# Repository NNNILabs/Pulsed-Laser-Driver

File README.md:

# Pulsed Laser Driver

<p align="center">
    <b>Power uncorrupted.</b> -J. Williams
</p>

## Introduction
A good friend of mine was talking about his work at the Solid State Physics lab at TU Berlin. They are currently trying to build upon the work of Japanese researchers regarding UVC lasers. These lasers need short, sharp (that was an English adjective, in EE speak it's "fast rise time") current pulses to be properly evaluated. With The Art of Electronics: The X Chapters by my side, I decided to take this project up, and boy, was it worth it. 
## Project Motivation
Apparently pulsed laser drivers cost upwards of several tens of thousands of Euros, so being able to come up with a a solution (that will probably be orders of magnitude cheaper) would be a much welcome break to the Lab's budget. Since the requirements were not particularly challenging (~250V, 5A, 1us pulses), I decided it would be feasible to try making a pulsed current sink.
## Usage
### Specifications [temp: as promised]:
- 25ns rise/fall times
- 5A peak current
- 250V diode voltage
## List of Files
- Resources: 
  - Infographics
- Hardware: 
  - KiCAD PCB files
- Software:
  - Simulation: LTspice .asc file, libraries
## Application Examples
[under construction]
## Notes
- Laser diodes usually with several volts across them. Since this UVC laser is under on-wafer testing, the methods of supplying power to the die involve high-resistance contacts: needles on pads, hence the need for high voltages.
- The choice of LT1193 was arbitrary - there are op-amps available that are better suited to the task, but I wanted an excuse to use the LT1193 because of its unique inputs which enable it to Kelvin-sense the input signal and feedback from the shunt. 
- Rise time measurements in LTspice of initial simulation using an AO6408 (10nH, 10pF parasitics):

- Rise time measurement with GaN FET (GS66502) (10nH, 10pF parasitics):

- GaN FETs which feature input, output and feedback capacitances that are at least an order of magnitude smaller than their regular silicon counterparts, are ideal for this application. Because of the low input capacitance (and the fact that the input capacitance is bootstrapped by Gm x source shunt resistor), the driving op-amp sees a significantly reduced capacitive load. On resistance and threshold voltage is comparable to a regular small switching MOSFET, but the drain-source breakdown voltage is significantly higher, almost touching 1kV. Of course, regular MOSFETs (or even a cascode to get the best of both worlds - easy drive with lots of transconductance and high-voltage drive capability) can be used with appropriate compensation "for the sake of a challenge", but GaN FETs save a lot of blood, sweat and tears.
- I decided to try using a smaller shunt resistor so the op-amp wouldn't have to swing as much to drive the gate and shunt voltage. This should theoretically increase bandwidth and therefore speed, but it did the opposite. One theory is that the threshold voltage of the MOSFET is much higher than the shunt voltage, so a smaller shunt voltage would mean a larger difference between it and gate threshold, so larger swing to get the same result. But a higher shunt voltage also means higher overall op-amp output, which should have a slowing effect. The answer can be found in AoE X - a higher shunt resistance means a higher bootstrapping voltage across gate-source capacitance through FET transconductance. 

## Links
- https://x.artofelectronics.net/
  - pg. 193 3x.5 "MOSFETs as Linear Transistors"
  - pg. 206 3x.7 "Bandwidth of the Cascode; BJT versus FET"
  - pg. 386 4x.26 "Nodal Loop Analysis: MOSFET Current Source"
- https://www.analog.com/media/en/technical-documentation/data-sheets/1193fb.pdf
- https://www.analog.com/media/en/technical-documentation/application-notes/an133f.pdf
- https://gansystems.com/wp-content/uploads/2022/07/GS-065-008-1-L-DS-Rev-220712.pdf

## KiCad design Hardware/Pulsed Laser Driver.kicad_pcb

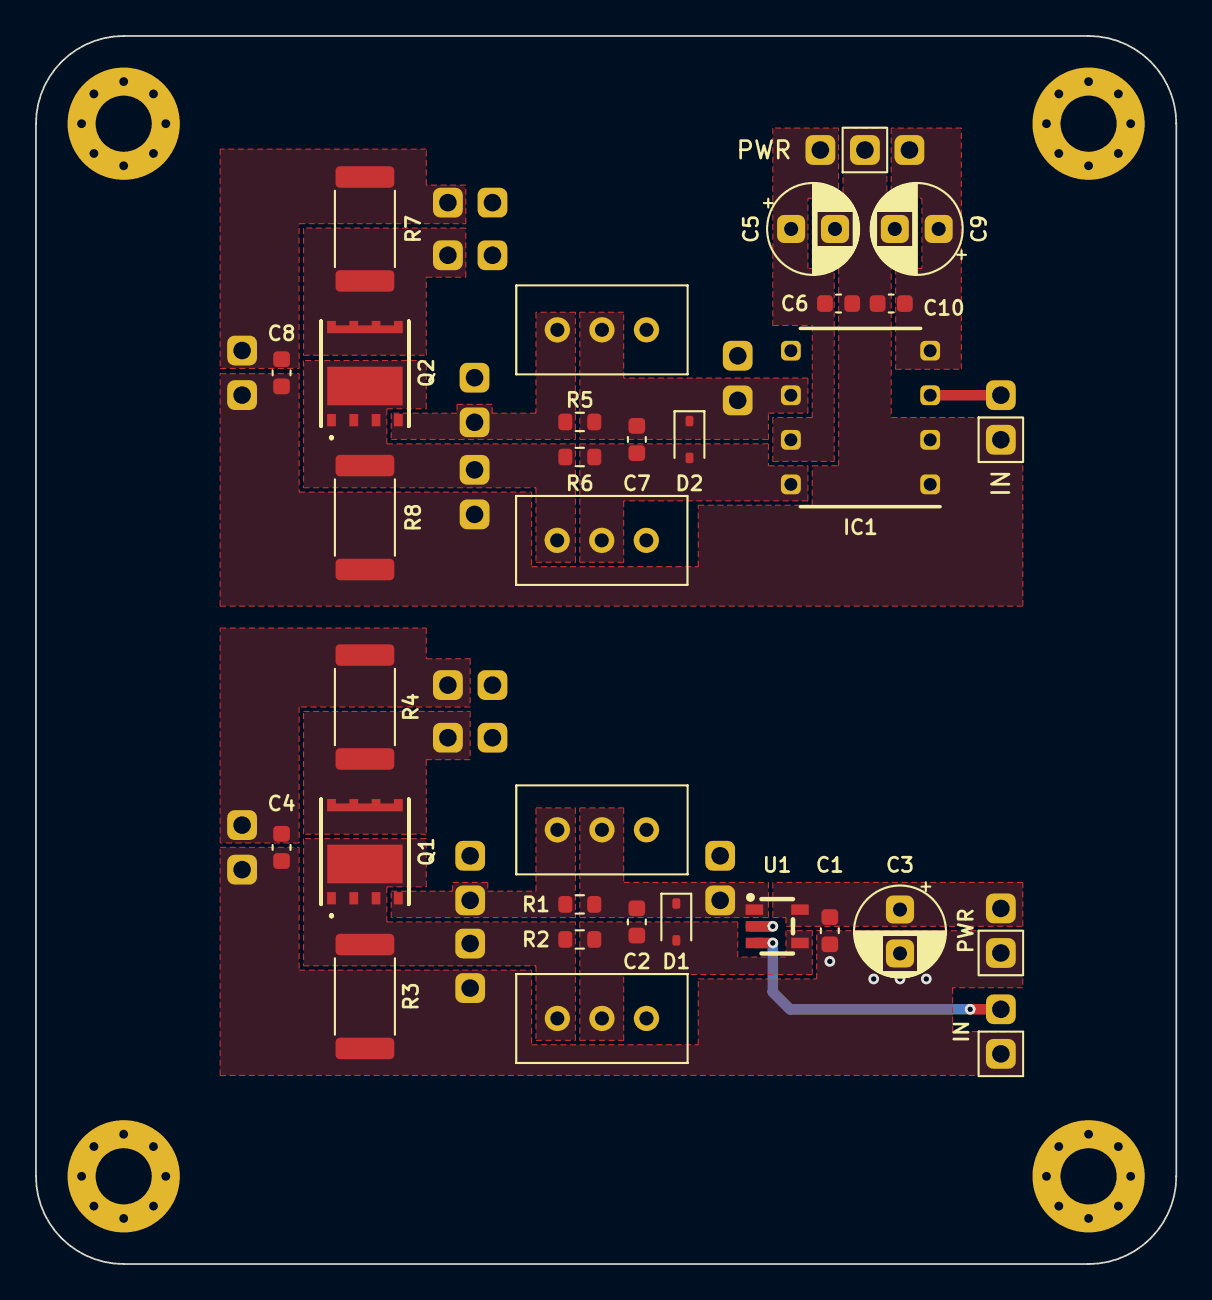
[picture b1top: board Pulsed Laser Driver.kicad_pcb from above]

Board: 2 copper layers, 65.0 x 70.0 mm, 34 parts (0 on the bottom side), 16 nets.

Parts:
C1, C4, C6, C8, C10: 10uF; C_0603_1608Metric
C2, C7: C; C_0603_1608Metric
C3, C5, C9: 22uF; CP_Radial_D5.0mm_P2.50mm
D1, D2: 4148; D_SOD-323
H1, H2, H3, H4: MountingHole; MountingHole_3.2mm_M3_Pad_Via
IC1: LT1193; DIP794W53P254L1016H394Q8N
J1, J2, J5, J6: IN; PinHeader_1x02_P2.54mm_Vertical
J3: PWR; PinHeader_1x03_P2.54mm_Vertical
J3#2: PWR; PinHeader_1x02_P2.54mm_Vertical
Q1, Q2: GS-065-008-1-L; GS0650081L
R1, R2, R5, R6: R; R_0603_1608Metric
R3, R8: 0R5; R_2512_6332Metric
R4, R7: HACK; R_2512_6332Metric
U1: ADA4891; SOT-23-5_L3.0-W1.7-P0.95-LS2.8-BR

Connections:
+5V: C1.2, C3.1, C5.1, C6.2, IC1.7 (V+), J3.1, J3#2.1, U1.5 (V+)
-5V: C9.1, C10.2, IC1.4 (V-), J3.3
/SOURCE: Q1.1, Q1.2, Q1.3, Q1.6, Q2.1, Q2.2, Q2.3, Q2.6, R2.2, R3.1, R6.2, R8.1
GND: C1.1, C3.2, C4.1, C5.2, C6.1, C8.1, C9.2, C10.1, IC1.1 (+~REF), IC1.2 (-IN), J1.2, J2.2, J3.2, J3#2.2, J5.2, J6.2, R3.2, R8.2, U1.2 (V-)
unnamed: C2.2, D1.2 (A), R2.1, U1.4 (-)
unnamed: C2.1, D1.1 (K), R1.1, U1.1
unnamed: C7.2, D2.2 (A), IC1.8 (-~FB), R6.1
unnamed: C7.1, D2.1 (K), IC1.6 (OUT), R5.1
unnamed: IC1.3 (+IN), J5.1
unnamed: J1.1, U1.3 (+)
unnamed: C4.2, J2.1, R4.1
unnamed: C8.2, J6.1, R7.1
unnamed: Q1.4, R1.2
unnamed: Q1.5, Q1.7, Q1.8, Q1.9, Q1.10, R4.2
unnamed: Q2.4, R5.2
unnamed: Q2.5, Q2.7, Q2.8, Q2.9, Q2.10, R7.2

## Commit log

2023-01-08 organization
2023-01-08 updated files
2023-03-07 updated infographics
2023-04-01 added hardware performance scope shot
2023-04-01 updated simulation files
2024-01-27 sync update
